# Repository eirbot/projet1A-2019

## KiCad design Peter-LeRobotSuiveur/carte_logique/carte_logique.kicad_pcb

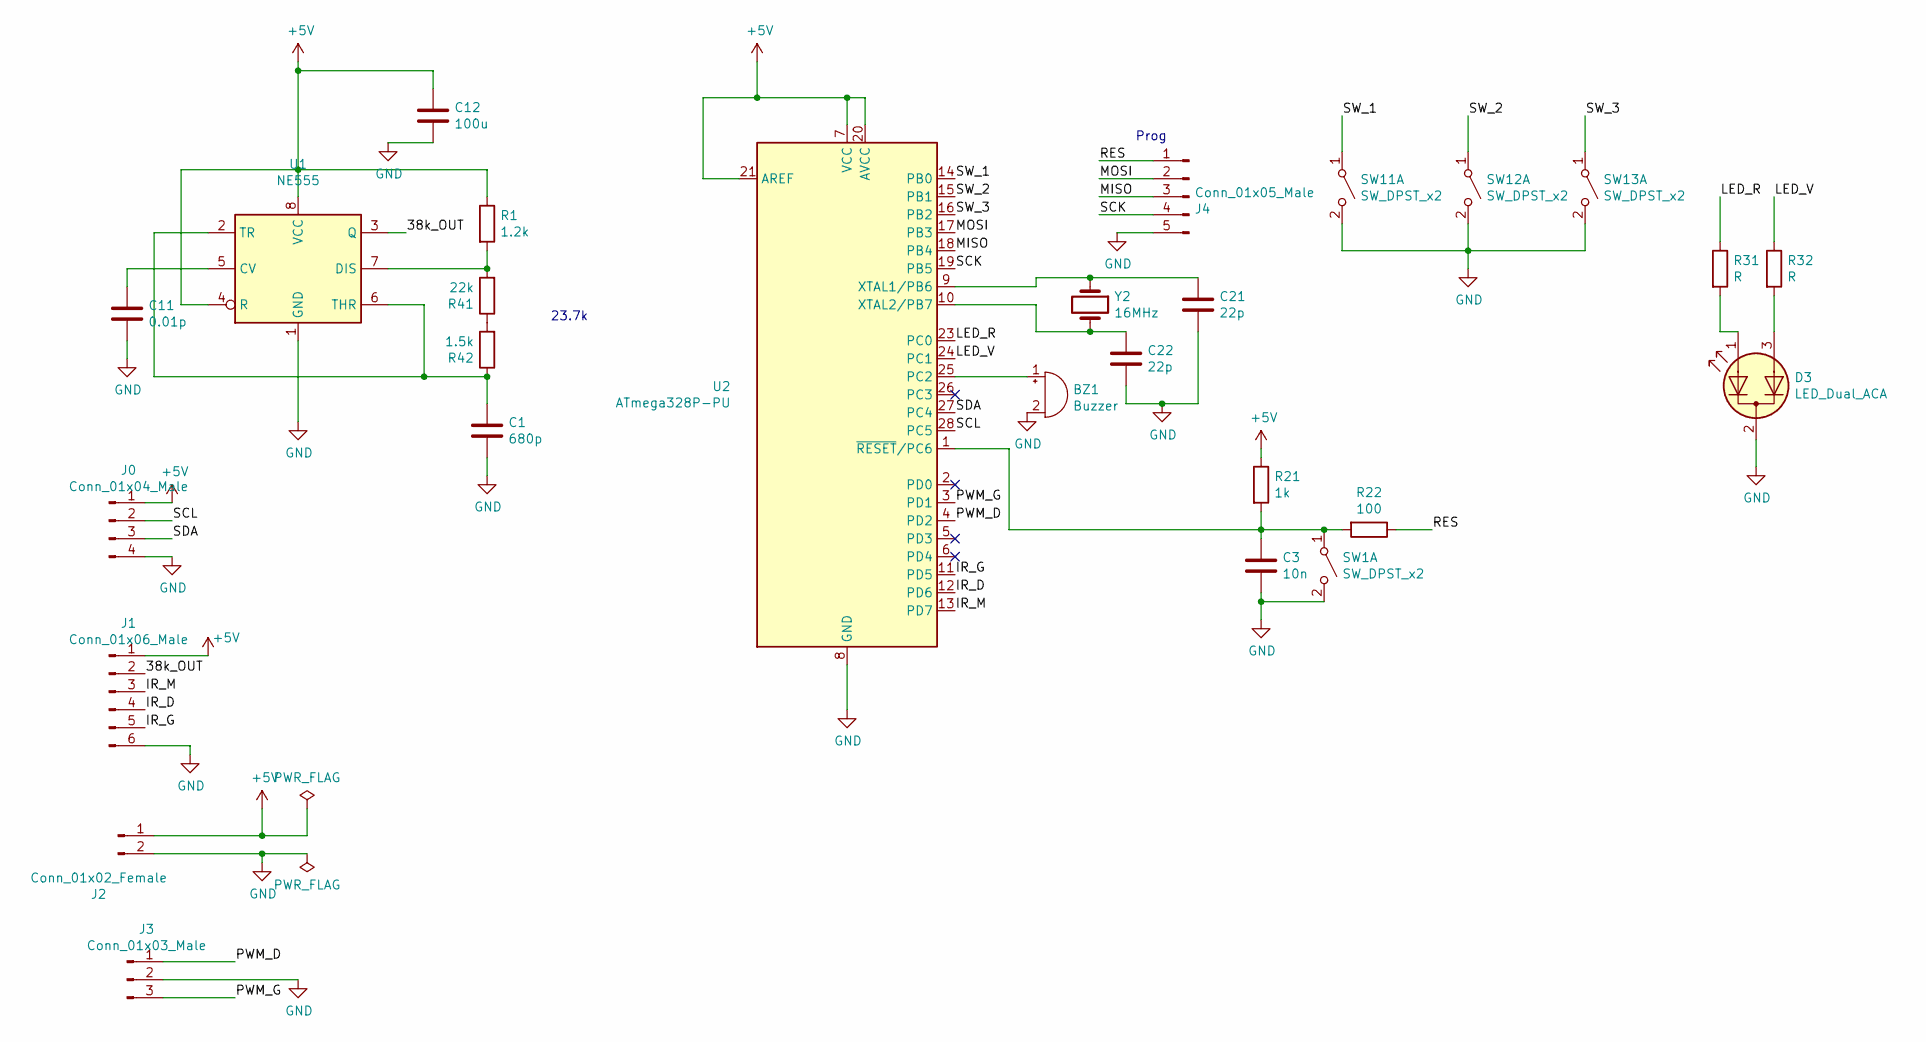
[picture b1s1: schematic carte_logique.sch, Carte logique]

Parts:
BZ1: Buzzer; Buzzer_15x7.5RM5.7
C1: 680p; C_Disc_D3.0mm_W1.6mm_P2.50mm
C3: 10n; C_Rect_L10.0mm_W2.5mm_P7.50mm_MKS4
C11: 0.01p; C_Disc_D3.0mm_W1.6mm_P2.50mm
C12: 100u; CP_Radial_D5.0mm_P2.50mm
C21, C22: 22p; C_Disc_D3.0mm_W1.6mm_P2.50mm
D3: LED_Dual_ACA; LED_D10.0mm-3
J0: Conn_01x04_Male; PinHeader_1x04_P2.54mm_Vertical
J1: Conn_01x06_Male; Molex_Micro-Latch_53254-0670_1x06_P2.00mm_Horizontal
J2: Conn_01x02_Female; TerminalBlock_bornier-2_P5.08mm
J3: Conn_01x03_Male; Molex_Micro-Latch_53254-0370_1x03_P2.00mm_Horizontal
J4: Conn_01x05_Male; PinHeader_1x05_P2.54mm_Vertical
R1: 1.2k; R_Axial_DIN0309_L9.0mm_D3.2mm_P12.70mm_Horizontal
R21: 1k; R_Axial_DIN0309_L9.0mm_D3.2mm_P12.70mm_Horizontal
R22: 100; R_Axial_DIN0309_L9.0mm_D3.2mm_P12.70mm_Horizontal
R31, R32: R; R_Axial_DIN0309_L9.0mm_D3.2mm_P12.70mm_Horizontal
R41: 22k; R_Axial_DIN0309_L9.0mm_D3.2mm_P12.70mm_Horizontal
R42: 1.5k; R_Axial_DIN0309_L9.0mm_D3.2mm_P12.70mm_Horizontal
SW1, SW11, SW12, SW13: SW_DPST_x2; SW_PUSH_6mm
U1: NE555; DIP-8_W7.62mm
U2: ATmega328P-PU; DIP-28_W7.62mm
Y2: 16MHz; Crystal_HC18-U_Vertical

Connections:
+5V: C12.1, J0.1, J1.1, J2.1, R1.1, R21.1, U1.4 (R), U1.8 (VCC), U2.7 (VCC), U2.20 (AVCC), U2.21 (AREF)
/38k_OUT: J1.2, U1.3 (Q)
/IR_D: J1.4, U2.12 (PD6)
/IR_G: J1.5, U2.11 (PD5)
/IR_M: J1.3, U2.13 (PD7)
/LED_R: R31.1, U2.23 (PC0)
/LED_V: R32.1, U2.24 (PC1)
/MISO: J4.3, U2.18 (PB4)
/MOSI: J4.2, U2.17 (PB3)
/PWM_D: J3.1, U2.4 (PD2)
/PWM_G: J3.3, U2.3 (PD1)
/RES: J4.1, R22.1
/SCK: J4.4, U2.19 (PB5)
/SCL: J0.2, U2.28 (PC5)
/SDA: J0.3, U2.27 (PC4)
/SW_1: SW11.1 (A), U2.14 (PB0)
/SW_2: SW12.1 (A), U2.15 (PB1)
/SW_3: SW13.1 (A), U2.16 (PB2)
GND: BZ1.2 (+), C1.2, C3.2, C11.2, C12.2, C21.1, C22.1, D3.2 (K), J0.4, J1.6, J2.2, J3.2, J4.5, SW1.2 (B), SW11.2 (B), SW12.2 (B), SW13.2 (B), U1.1 (GND), U2.8 (GND), U2.22 (GND)
unnamed: BZ1.1 (-), U2.25 (PC2)
unnamed: C1.1, R42.1, U1.2 (TR), U1.6 (THR)
unnamed: C3.1, R21.2, R22.2, SW1.1 (A), U2.1 (~RESET~/PC6)
unnamed: C11.1, U1.5 (CV)
unnamed: C21.2, U2.9 (XTAL1/PB6), Y2.1
unnamed: C22.2, U2.10 (XTAL2/PB7), Y2.2
unnamed: D3.1 (A1), R31.2
unnamed: D3.3 (A2), R32.2
unnamed: R1.2, R41.2, U1.7 (DIS)
unnamed: R41.1, R42.2

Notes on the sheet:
Prog
23.7k

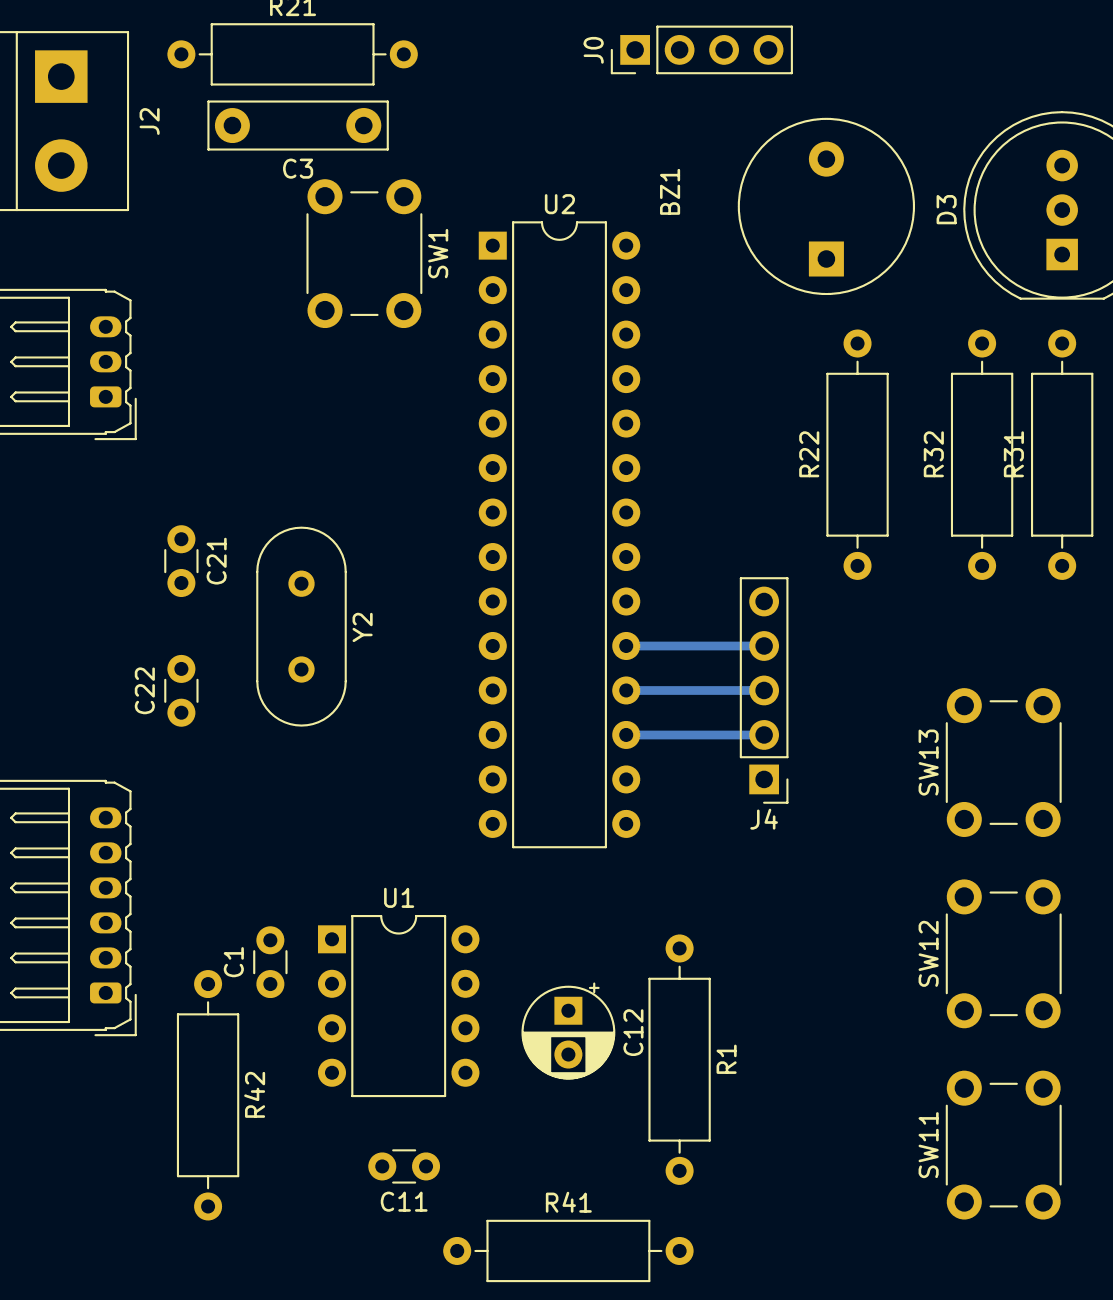
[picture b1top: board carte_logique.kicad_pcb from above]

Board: 2 copper layers, 27 parts (0 on the bottom side), 29 nets.

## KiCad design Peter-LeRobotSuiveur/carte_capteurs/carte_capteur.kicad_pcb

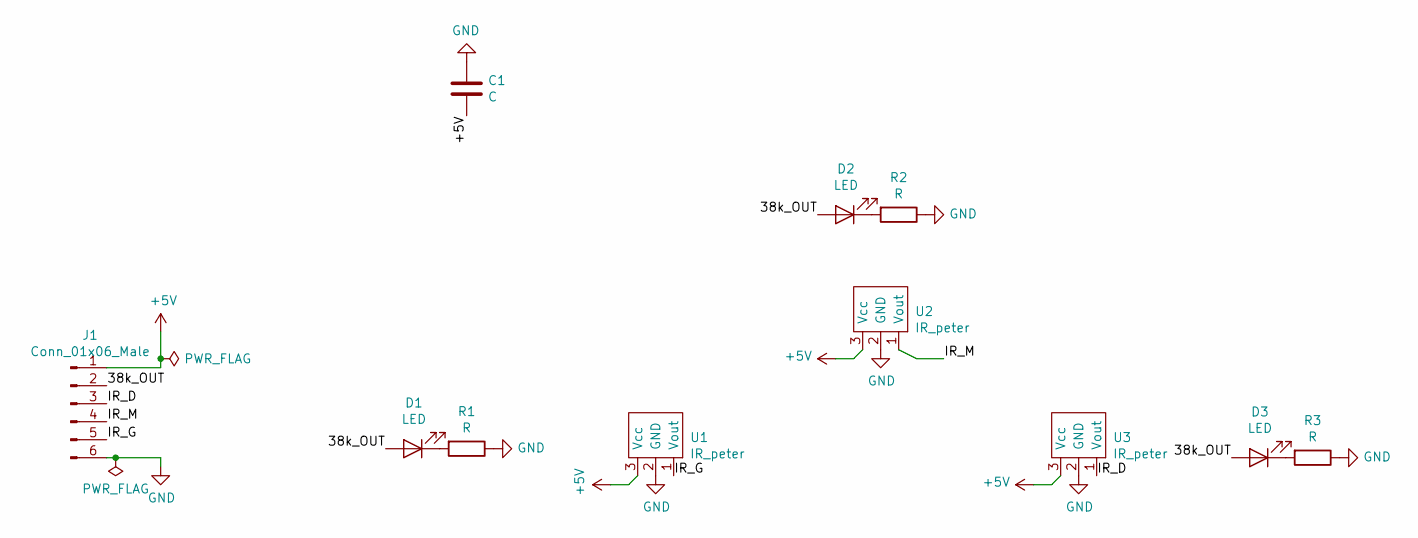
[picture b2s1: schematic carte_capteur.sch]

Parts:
C1: C; CP_Axial_L10.0mm_D4.5mm_P15.00mm_Horizontal
D1, D2, D3: LED; LED_D5.0mm_IRBlack
J1: Conn_01x06_Male; Molex_Micro-Latch_53254-0670_1x06_P2.00mm_Horizontal
R1, R2, R3: R; R_Axial_DIN0309_L9.0mm_D3.2mm_P12.70mm_Horizontal
U1, U2, U3: IR_peter; SIPAK_Vertical

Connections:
+5V: C1.2, J1.1, U1.3 (Vcc), U2.3 (Vcc), U3.3 (Vcc)
/38k_OUT: D1.2 (A), D2.2 (A), D3.2 (A), J1.2
/IR_D: J1.3, U3.1 (Vout)
/IR_G: J1.5, U1.1 (Vout)
/IR_M: J1.4, U2.1 (Vout)
GND: C1.1, J1.6, R1.1, R2.1, R3.1, U1.2 (GND), U2.2 (GND), U3.2 (GND)
unnamed: D1.1 (K), R1.2
unnamed: D2.1 (K), R2.2
unnamed: D3.1 (K), R3.2

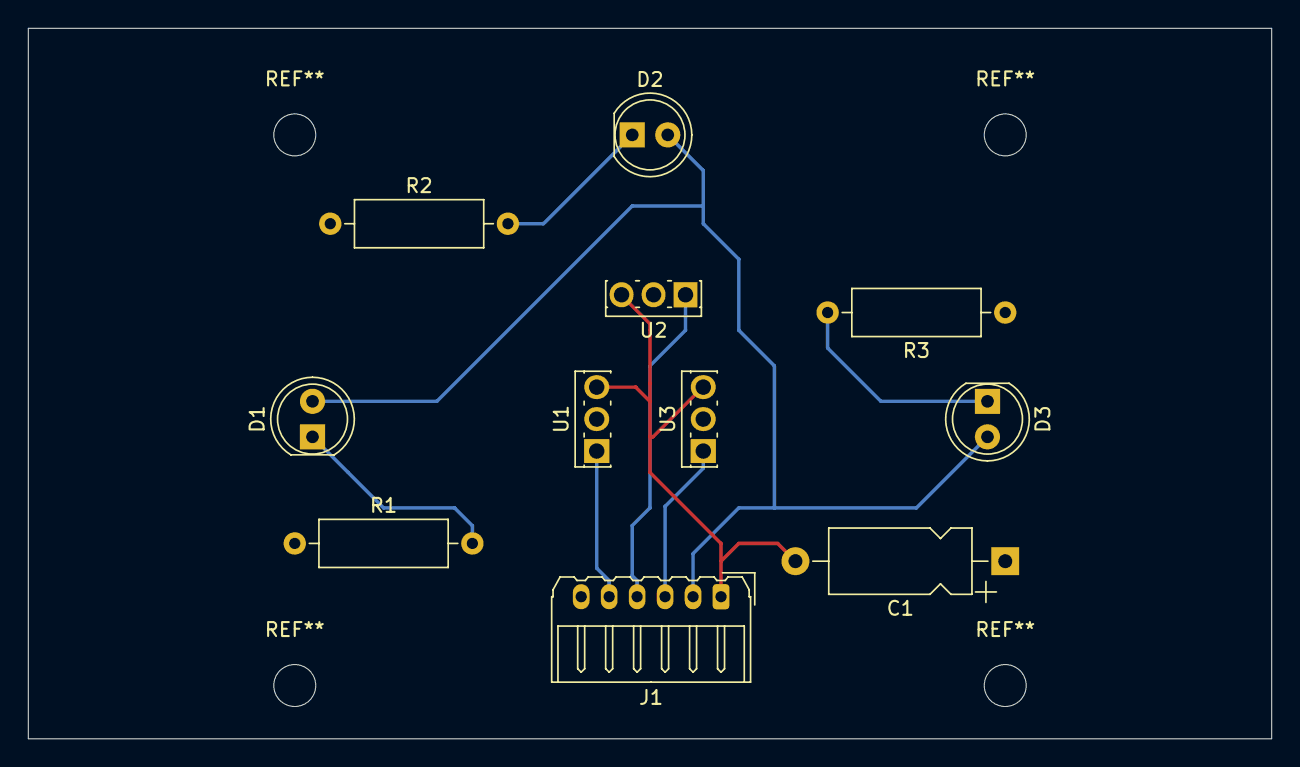
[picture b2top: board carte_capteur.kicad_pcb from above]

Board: 2 copper layers, 88.9 x 50.8 mm, 11 parts (0 on the bottom side), 9 nets.
